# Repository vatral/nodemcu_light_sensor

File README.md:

# nodemcu_light_sensor
NodeMCU light level sensor

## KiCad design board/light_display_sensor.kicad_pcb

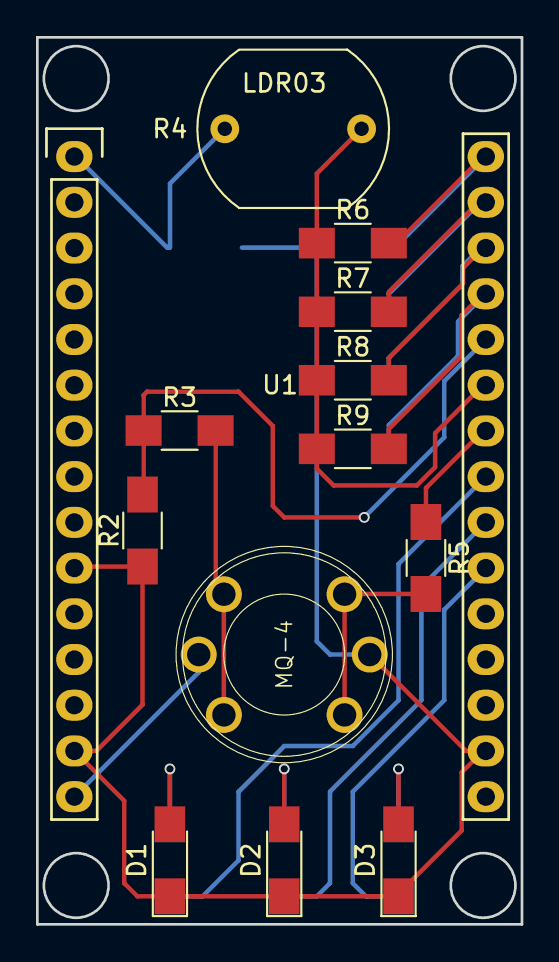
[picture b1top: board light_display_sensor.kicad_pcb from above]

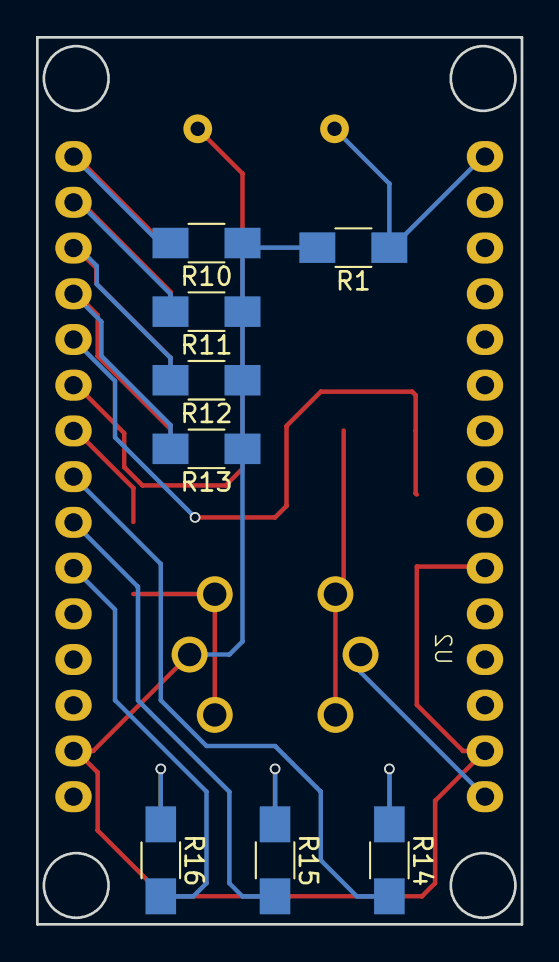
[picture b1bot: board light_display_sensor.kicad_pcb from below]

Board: 2 copper layers, 26.9 x 49.3 mm, 21 parts (8 on the bottom side), 17 nets.

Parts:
D1: Pwr; LED_1206_HandSoldering
D2: Act; LED_1206_HandSoldering
D3: Err; LED_1206_HandSoldering
R1, R14, R15, R16: 1k; R_1206_HandSoldering
R2: 20k; R_1206_HandSoldering
R3, R5, R10, R11, R12, R13: 10k; R_1206_HandSoldering
R4: LDR03; Resistor_LDR_10x8.5_RM7.6
R6, R7, R8, R9: 0; R_1206_HandSoldering
U1: NodeMCU_Amica_R2
U2: MQ-4; OPL-sensor-SNR6-D19.0MM

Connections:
+3V3: R4.1, R6.1, R7.1, R8.1, R9.1, U1.11, U1.16, U1.25
GND: D1.1, D2.1, D3.1, R1.2, R2.1, R5.1, R10.1, R11.1, R12.1, R13.1, U1.10, U1.14, U1.17, U1.24, U2.6
unnamed: D1.2, R14.1
unnamed: D2.2, R15.1
unnamed: D3.2, R16.1
unnamed: R1.1, R4.2, U1.1
unnamed: R2.2, R3.1, U1.26
unnamed: R3.2, U2.1, U2.3
unnamed: R5.2, U2.2, U2.4
unnamed: R6.2, R10.2, U1.30
unnamed: R7.2, R11.2, U1.29
unnamed: R8.2, R12.2, U1.28
unnamed: R9.2, R13.2, U1.27
unnamed: R14.2, U1.23
unnamed: R15.2, U1.22
unnamed: R16.2, U1.21
unnamed: U1.15, U2.5

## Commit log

2018-09-20 Initial version
